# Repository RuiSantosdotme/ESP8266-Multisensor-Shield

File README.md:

# ESP8266 Multisensor Shield

In this project you’ll discover how to design and create a Multisensor Shield for the ESP8266 Wemos D1 Mini board. The shield has temperature sensor (DS18B20), a PIR motion sensor, an LDR, and a terminal to connect a relay module. We'll start by preparing all the hardware and then program it.

Watch the video tutorial "Build a Multisensor Shield for ESP8266 - Part 1": https://youtu.be/nKFsNM5Q00k

Watch the video tutorial "Programming Multisensor Shield for ESP8266 - Part 2": https://youtu.be/hxRqLIfabqw

For the complete step-by-step instructions, visit: https://randomnerdtutorials.com/esp8266-multisensor-shield/

How to browse the GitHub repository:
- [ESP8266 web server code (for Arduino IDE)](https://github.com/RuiSantosdotme/ESP8266-Multisensor-Shield/blob/master/Code/ESP8266_Multisensor_Shield/ESP8266_Multisensor_Shield.ino)
- [ESP8266 with Node-RED](https://github.com/RuiSantosdotme/ESP8266-Multisensor-Shield/tree/master/Code/NodeRED_ESP8266_Multisensor_Shield)
- [Schematic diagram](https://github.com/RuiSantosdotme/ESP8266-Multisensor-Shield/tree/master/Images)
- [Gerber files](https://github.com/RuiSantosdotme/ESP8266-Multisensor-Shield/raw/master/KiCad_PCB_ESP8266_Multisensor_Shield/GERBERS/WemosD1MiniShield.zip)
- [KiCad project to edit the PCB](https://github.com/RuiSantosdotme/ESP8266-Multisensor-Shield/tree/master/KiCad_PCB_ESP8266_Multisensor_Shield)
- [3D Enclosure (STL files and SketchUp Project)](https://github.com/RuiSantosdotme/ESP8266-Multisensor-Shield/tree/master/3D_Enclosure)
- [Click here to download all the files](https://github.com/RuiSantosdotme/ESP8266-Multisensor-Shield/archive/master.zip)

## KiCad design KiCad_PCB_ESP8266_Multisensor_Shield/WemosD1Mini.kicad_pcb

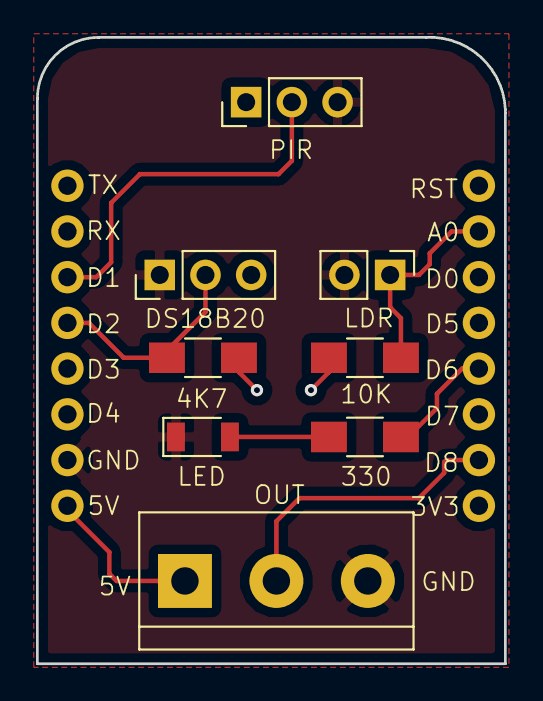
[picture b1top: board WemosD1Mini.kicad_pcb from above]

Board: 2 copper layers, 26.0 x 34.8 mm, 9 parts (0 on the bottom side), 9 nets.

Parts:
4K7: 4K7; R_1206_HandSoldering
10K: 10K; R_1206_HandSoldering
330: 330; R_1206_HandSoldering
LED: LED; D_1206
R4: LDR; Pin_Header_Straight_1x02_Pitch2.54mm
U1: DS18B20; Pin_Header_Straight_1x03_Pitch2.54mm
U2: PIR; Pin_Header_Straight_1x03_Pitch2.54mm
U3: WeMos_mini; Wemos_D1_Mini_Shield_No_SilkS
U4: RELAY_3_PINS; TerminalBlock_bornier-3_P5.08mm

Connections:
+3V3: 4K7.2, 10K.2, U1.3, U2.1, U3.16
+5V: U3.1, U4.1
GND: LED.1, R4.2, U1.1, U2.3, U3.2, U4.3
unnamed: 330.1, LED.2
unnamed: 4K7.1, U1.2, U3.5
unnamed: 330.2, U3.13
unnamed: 10K.1, R4.1, U3.10
unnamed: U2.2, U3.6
unnamed: U3.15, U4.2

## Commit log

2018-08-30 KiCad project, Images, and Arduino code
2018-09-04 3D Enclosure, Code updated, and Readme
2018-09-04 Readme updated
2018-09-13 ESP8266 Multisensor Shield Node-RED
2018-09-13 Node-RED flow example screenshot
